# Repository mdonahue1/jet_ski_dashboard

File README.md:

# jet_ski_dashboard
create dashboard for 1989 seadoo sp

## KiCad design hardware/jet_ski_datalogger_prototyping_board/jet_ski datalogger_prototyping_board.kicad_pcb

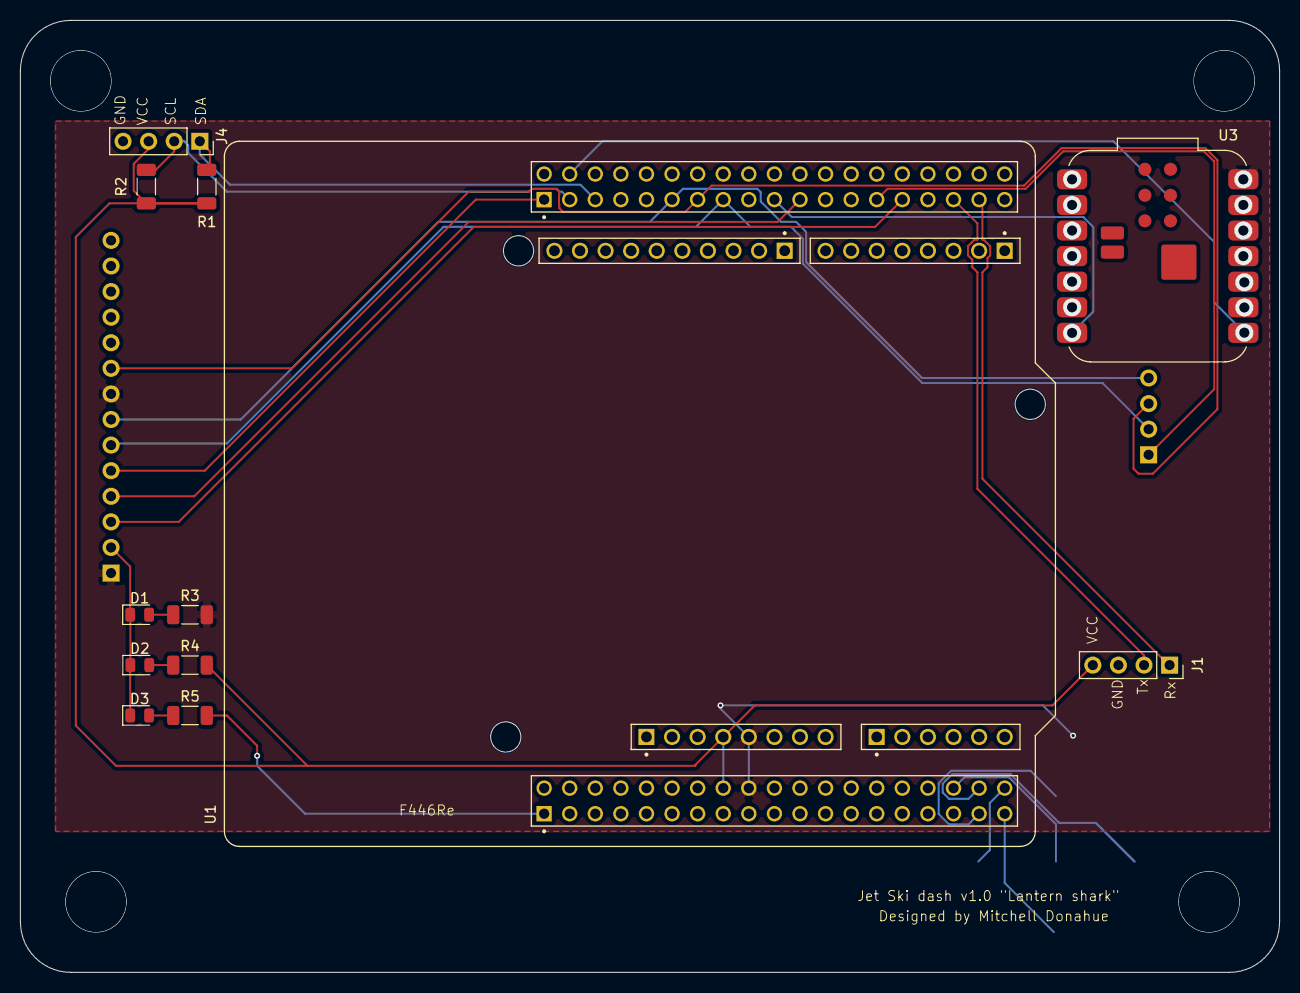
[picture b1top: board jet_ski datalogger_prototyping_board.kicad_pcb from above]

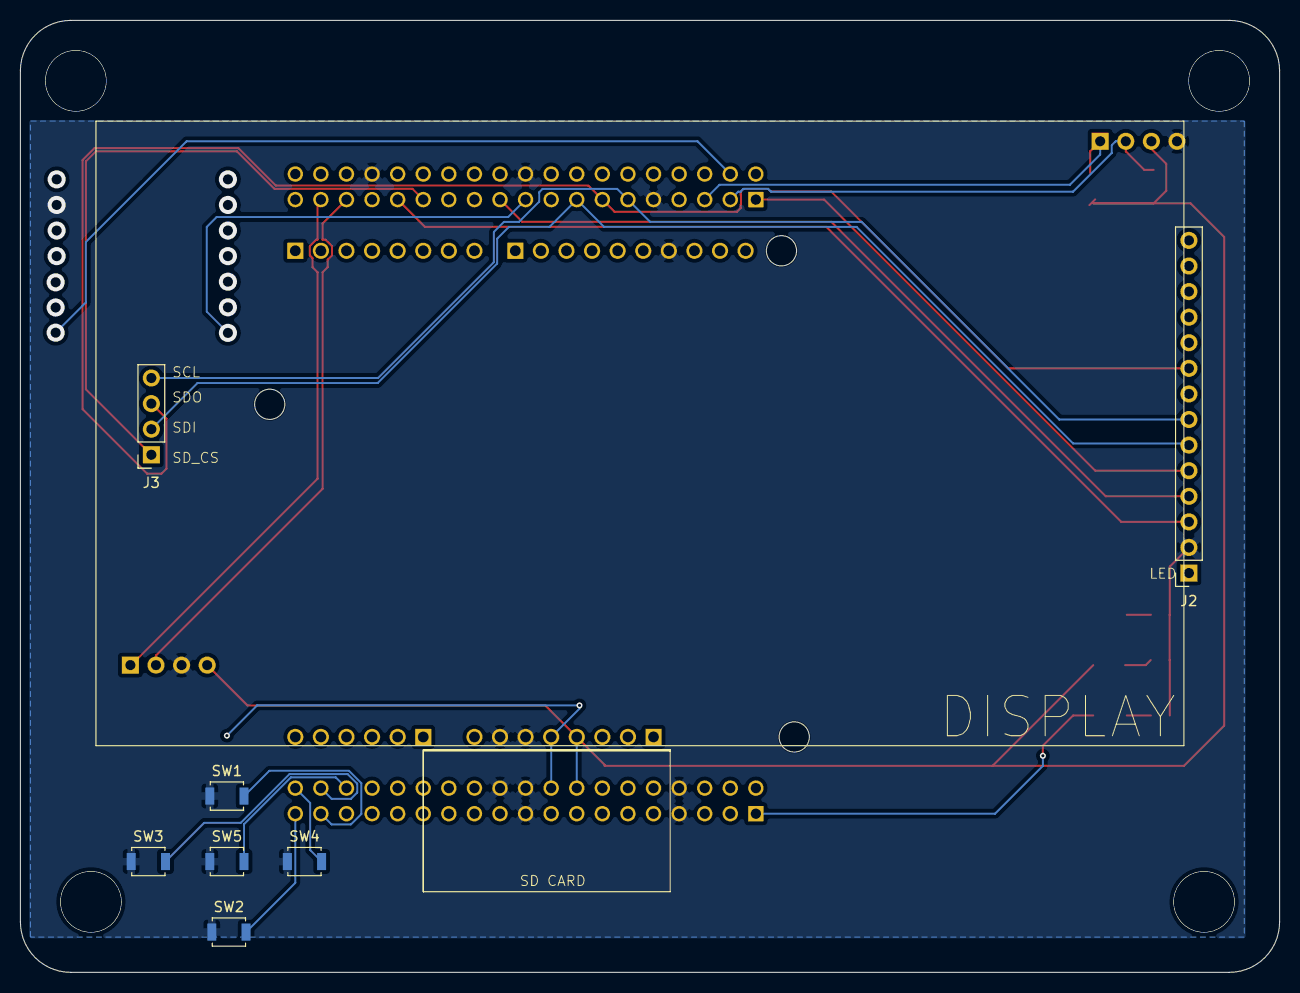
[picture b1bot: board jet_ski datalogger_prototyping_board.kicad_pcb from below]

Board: 2 copper layers, 125.0 x 94.5 mm, 19 parts (7 on the bottom side), 25 nets.

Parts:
D1, D2, D3: LED; LED_0805_2012Metric
J1: gps module; PinSocket_1x04_P2.54mm_Vertical
J2: Display Socket; PinSocket_1x14_P2.54mm_Vertical
J3: SD Card reader; PinSocket_1x04_P2.54mm_Vertical
J4: I2C conn; PinSocket_1x04_P2.54mm_Vertical
R1, R2: 4.7K; L_1206_3216Metric_Pad1.22x1.90mm_HandSolder
R3, R4, R5: 1K; L_1206_3216Metric_Pad1.22x1.90mm_HandSolder
SW1: UP; SW_SPST_B3U-1000P
SW2: DOWN; SW_SPST_B3U-1000P
SW3: Left; SW_SPST_B3U-1000P
SW4: RIGHT; SW_SPST_B3U-1000P
SW5: Select; SW_SPST_B3U-1000P
U1: NUCLEO-F446RE; MODULE_NUCLEO-F446RE
U3: XIAO-ESP32-C6-SMD; MCU_Seeed_ESP32C3

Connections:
3.3v indicator: J1.4, J4.3, R1.2, R2.1, U1.CN6_4 (CN6_+3V3)
Cs: J2.3, U1.CN10_29 (PB5)
DC/RS: J2.5, U1.CN10_1 (PC9)
GND: D1.1 (K), D2.1 (K), D3.1 (K), J1.3, J2.2, J4.4, SW1.1 (A), SW2.1 (A), SW3.1 (A), SW4.1 (A), SW5.1 (A), U1.CN5_7 (CN5_GND), U1.CN6_6 (CN6_GND), U1.CN6_7 (CN6_GND), U1.CN7_7 (BOOT0), U1.CN7_8 (CN7_GND), U1.CN7_19 (CN7_GND), U1.CN7_20 (CN7_GND), U1.CN7_22 (CN7_GND), U1.CN10_9 (CN10_GND), U1.CN10_20 (CN10_GND), U1.CN10_32 (AGND), U3.13 (GND)
GPS_Rx: J1.1, U1.CN10_35 (PA2)
GPS_Tx: J1.2, U1.CN10_33 (PA10)
I2C SCL: J4.2, R2.2, U1.CN10_3 (PB8)
I2C SDA: J4.1, R1.1, U1.CN10_5 (PB9)
LED: J2.1, J2.8, R3.2, U1.CN6_5 (CN6_+5V), U1.CN7_18 (CN7_+5V), U3.14 (VBUS)
unnamed: D1.2 (A), R3.1
unnamed: D2.2 (A), R4.1
unnamed: D3.2 (A), R5.1
unnamed: SW1.2 (B), U1.CN7_35 (PC2)
unnamed: SW2.2 (B), U1.CN7_37 (PC3)
unnamed: SW3.2 (B), U1.CN7_36 (PC1/PB9)
unnamed: SW4.2 (B), U1.CN7_38 (PC0/PB8)
unnamed: SW5.2 (B), U1.CN7_34 (PB0)
Reset: J2.4, U1.CN10_21 (PA9)
SCK: J2.7, J3.4, U1.CN10_11 (PA5)
SDI: J2.6, J3.2, U1.CN10_15 (PA7)
SDO: J2.9, J3.3, U1.CN10_13 (PA6)
SD_CS: J3.1, U1.CN10_27 (PB4)
Status_indicator: R5.2, U1.CN7_1 (PC10)
Xiao Rx: U1.CN10_4 (PC6), U3.8 (D7)
Xiao Tx: U1.CN10_19 (PC7), U3.7 (D6)

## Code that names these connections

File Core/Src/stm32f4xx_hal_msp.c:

/* USER CODE BEGIN Header */
/**
  ******************************************************************************
  * @file         stm32f4xx_hal_msp.c
  * @brief        This file provides code for the MSP Initialization
  *               and de-Initialization codes.
  ******************************************************************************
  * @attention
  *
  * Copyright (c) 2026 STMicroelectronics.
  * All rights reserved.
  *
  * This software is licensed under terms that can be found in the LICENSE file
  * in the root directory of this software component.
  * If no LICENSE file comes with this software, it is provided AS-IS.
  *
  ******************************************************************************
  */
/* USER CODE END Header */

/* Includes ------------------------------------------------------------------*/
#include "main.h"
/* USER CODE BEGIN Includes */

/* USER CODE END Includes */

/* Private typedef -----------------------------------------------------------*/
/* USER CODE BEGIN TD */

/* USER CODE END TD */

/* Private define ------------------------------------------------------------*/
/* USER CODE BEGIN Define */

/* USER CODE END Define */

/* Private macro -------------------------------------------------------------*/
/* USER CODE BEGIN Macro */

/* USER CODE END Macro */

/* Private variables ---------------------------------------------------------*/
/* USER CODE BEGIN PV */

/* USER CODE END PV */

/* Private function prototypes -----------------------------------------------*/
/* USER CODE BEGIN PFP */

/* USER CODE END PFP */

/* External functions --------------------------------------------------------*/
/* USER CODE BEGIN ExternalFunctions */

/* USER CODE END ExternalFunctions */

/* USER CODE BEGIN 0 */

/* USER CODE END 0 */
/**
  * Initializes the Global MSP.
  */
void HAL_MspInit(void)
{

  /* USER CODE BEGIN MspInit 0 */

  /* USER CODE END MspInit 0 */

  __HAL_RCC_SYSCFG_CLK_ENABLE();
  __HAL_RCC_PWR_CLK_ENABLE();

  HAL_NVIC_SetPriorityGrouping(NVIC_PRIORITYGROUP_0);

  /* System interrupt init*/

  /* USER CODE BEGIN MspInit 1 */

  /* USER CODE END MspInit 1 */
}

/**
  * @brief SPI MSP Initialization
  * This function configures the hardware resources used in this example
  * @param hspi: SPI handle pointer
  * @retval None
  */
void HAL_SPI_MspInit(SPI_HandleTypeDef* hspi)
{
  GPIO_InitTypeDef GPIO_InitStruct = {0};
  if(hspi->Instance==SPI1)
  {
    /* USER CODE BEGIN SPI1_MspInit 0 */

    /* USER CODE END SPI1_MspInit 0 */
    /* Peripheral clock enable */
    __HAL_RCC_SPI1_CLK_ENABLE();

    __HAL_RCC_GPIOA_CLK_ENABLE();
    /**SPI1 GPIO Configuration
    PA5     ------> SPI1_SCK
    PA6     ------> SPI1_MISO
    PA7     ------> SPI1_MOSI
    */
    GPIO_InitStruct.Pin = GPIO_PIN_5|GPIO_PIN_6|GPIO_PIN_7;
    GPIO_InitStruct.Mode = GPIO_MODE_AF_PP;
    GPIO_InitStruct.Pull = GPIO_NOPULL;
    GPIO_InitStruct.Speed = GPIO_SPEED_FREQ_VERY_HIGH;
    GPIO_InitStruct.Alternate = GPIO_AF5_SPI1;
    HAL_GPIO_Init(GPIOA, &GPIO_InitStruct);

    /* USER CODE BEGIN SPI1_MspInit 1 */

    /* USER CODE END SPI1_MspInit 1 */

  }

}

/**
  * @brief SPI MSP De-Initialization
  * This function freeze the hardware resources used in this example
  * @param hspi: SPI handle pointer
  * @retval None
  */
void HAL_SPI_MspDeInit(SPI_HandleTypeDef* hspi)
{
  if(hspi->Instance==SPI1)
  {
    /* USER CODE BEGIN SPI1_MspDeInit 0 */

    /* USER CODE END SPI1_MspDeInit 0 */
    /* Peripheral clock disable */
    __HAL_RCC_SPI1_CLK_DISABLE();

    /**SPI1 GPIO Configuration
    PA5     ------> SPI1_SCK
    PA6     ------> SPI1_MISO
    PA7     ------> SPI1_MOSI
    */
    HAL_GPIO_DeInit(GPIOA, GPIO_PIN_5|GPIO_PIN_6|GPIO_PIN_7);

    /* USER CODE BEGIN SPI1_MspDeInit 1 */

    /* USER CODE END SPI1_MspDeInit 1 */
  }

}

/**
  * @brief UART MSP Initialization
  * This function configures the hardware resources used in this example
  * @param huart: UART handle pointer
  * @retval None
  */
void HAL_UART_MspInit(UART_HandleTypeDef* huart)
{
  GPIO_InitTypeDef GPIO_InitStruct = {0};
  if(huart->Instance==USART1)
  {
    /* USER CODE BEGIN USART1_MspInit 0 */

    /* USER CODE END USART1_MspInit 0 */
    /* Peripheral clock enable */
    __HAL_RCC_USART1_CLK_ENABLE();

    __HAL_RCC_GPIOA_CLK_ENABLE();
    /**USART1 GPIO Configuration
    PA10     ------> USART1_RX
    */
    GPIO_InitStruct.Pin = GPS_RX_Pin;
    GPIO_InitStruct.Mode = GPIO_MODE_AF_PP;
    GPIO_InitStruct.Pull = GPIO_NOPULL;
    GPIO_InitStruct.Speed = GPIO_SPEED_FREQ_VERY_HIGH;
    /*
     * Alternate function 7 connects PA10 to the USART1 peripheral internally.
     * After this, pin changes feed the UART hardware instead of normal GPIO reads.
     */
    GPIO_InitStruct.Alternate = GPIO_AF7_USART1;
    HAL_GPIO_Init(GPS_RX_GPIO_Port, &GPIO_InitStruct);

    /* USER CODE BEGIN USART1_MspInit 1 */
    /*
     * The UART IRQ is what lets gps.c receive one byte at a time without polling.
     * HAL_UART_IRQHandler() later calls HAL_UART_RxCpltCallback() in gps.c.
     */
    HAL_NVIC_SetPriority(USART1_IRQn, 0, 0);
    HAL_NVIC_EnableIRQ(USART1_IRQn);

    /* USER CODE END USART1_MspInit 1 */

  }
  else
  if(huart->Instance==USART2)
  {
    /* USER CODE BEGIN USART2_MspInit 0 */

    /* USER CODE END USART2_MspInit 0 */
    /* Peripheral clock enable */
    __HAL_RCC_USART2_CLK_ENABLE();

    __HAL_RCC_GPIOA_CLK_ENABLE();
    /**USART2 GPIO Configuration
    PA2     ------> USART2_TX
    PA3     ------> USART2_RX
    */
    GPIO_InitStruct.Pin = USART_TX_Pin|USART_RX_Pin;
    GPIO_InitStruct.Mode = GPIO_MODE_AF_PP;
    GPIO_InitStruct.Pull = GPIO_NOPULL;
    GPIO_InitStruct.Speed = GPIO_SPEED_FREQ_VERY_HIGH;
    GPIO_InitStruct.Alternate = GPIO_AF7_USART2;
    HAL_GPIO_Init(GPIOA, &GPIO_InitStruct);

    /* USER CODE BEGIN USART2_MspInit 1 */
    HAL_NVIC_SetPriority(USART2_IRQn, 0, 0);
    HAL_NVIC_EnableIRQ(USART2_IRQn);

    /* USER CODE END USART2_MspInit 1 */

  }

}

/**
  * @brief UART MSP De-Initialization
  * This function freeze the hardware resources used in this example
  * @param huart: UART handle pointer
  * @retval None
  */
void HAL_UART_MspDeInit(UART_HandleTypeDef* huart)
{
  if(huart->Instance==USART1)
  {
    /* USER CODE BEGIN USART1_MspDeInit 0 */

    /* USER CODE END USART1_MspDeInit 0 */
    /* Peripheral clock disable */
    __HAL_RCC_USART1_CLK_DISABLE();

    /**USART1 GPIO Configuration
    PA10     ------> USART1_RX
    */
    HAL_GPIO_DeInit(GPS_RX_GPIO_Port, GPS_RX_Pin);

    /* USER CODE BEGIN USART1_MspDeInit 1 */
    HAL_NVIC_DisableIRQ(USART1_IRQn);

    /* USER CODE END USART1_MspDeInit 1 */
  }
  else
  if(huart->Instance==USART2)
  {
    /* USER CODE BEGIN USART2_MspDeInit 0 */

    /* USER CODE END USART2_MspDeInit 0 */
    /* Peripheral clock disable */
    __HAL_RCC_USART2_CLK_DISABLE();

    /**USART2 GPIO Configuration
    PA2     ------> USART2_TX
    PA3     ------> USART2_RX
    */
    HAL_GPIO_DeInit(GPIOA, USART_TX_Pin|USART_RX_Pin);

    /* USER CODE BEGIN USART2_MspDeInit 1 */
    HAL_NVIC_DisableIRQ(USART2_IRQn);

    /* USER CODE END USART2_MspDeInit 1 */
  }

}

/* USER CODE BEGIN 1 */

/* USER CODE END 1 */

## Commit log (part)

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2026-05-28 initial upload
    main pcb design schematics(incomplete)
